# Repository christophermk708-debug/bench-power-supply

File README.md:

# bench-power-supply
# Adjustable Bench Power Supply

A from-scratch benchtop power supply: adjustable 1.4–11.9 V buck-regulated main output with live voltage/current display, plus fixed 5 V and 3.3 V rails. Designed in KiCad, fabricated by JLCPCB, hand-assembled, and brought up with a staged test procedure. 

## Specifications (measured)

| Parameter | Value |
|---|---|
| Input | 12 V DC barrel jack (center-positive, regulated) |
| Adjustable output | **1.4 – 11.9 V** (25-turn trimmer), ~2 A class |
| Fixed rails | 5.0 V (L7805) and 3.3 V (AMS1117) on headers |
| Metering | Panel voltmeter/ammeter on the adjustable output |
| Protection | Reverse-polarity Schottky (1N5822), 3 A resettable PTC fuse, per-rail decoupling |

## Design

- **LM2596-ADJ buck converter** for the main rail-switching regulation chosen over linear for efficiency at multi-amp loads. Output set by a feedback divider: `Vout = 1.23 × (1 + R_upper/R_lower)`, with a 25-turn trimmer as the adjustable element.
- **Fixed rails cascade from the buck's input**: the 7805 drops 12 V→5 V and the AMS1117 is fed *from the 5 V rail* rather than raw input to minimize dissipation.
- **Layout follows switching-supply practice**: the LM2596/inductor/catch-diode/capacitor loop is clustered tightly to minimize the switching current loop.

## Rev A findings — what the first board taught me

Every one of these was found by measurement during bring-up.

1. **D1 (reverse-polarity diode) was oriented backwards *in the schematic*.** The silkscreen reproduced the error, so the assembled board matched the design and this blocked all input power. Found by voltage tracing: ~12 V on the jack side of D1, ~1 V after it. Invisible to DRC and 3D review because the error was electrical, not mechanical. Fixed by desoldering and flipping the part.
2. **Maximum output was limited to 8.6 V by the feedback divider**, not by input headroom. Derived from the regulation equation: with R_lower = 1 kΩ, max Vout = 1.23 × (1 + 6k/1k) ≈ 8.6 V. Reworked R1 from 1 kΩ → 470 Ω on-board, raising the measured maximum to 11.9 V.
3. **J1 barrel jack footprint was placed rotated 180°** — the connector opening faced into the board. Resolved by flipping the 

## Bring-up lessons 

- A "12 V" wall adapter measured **25 V with no load**  it was an unregulated transformer type that only reaches nameplate under rated current. Replaced with a regulated switching adapter; my acceptance test is now a bare-plug measurement before any adapter touches a board.
- Mid-debug, **every reading came in almost exactly 2× high**  input, both fixed rails, even a USB 5 V reference. The multimeter's factory-included battery was dying, skewing its reference. Verified against known references (fresh AA cell, USB 5 V, the panel meter) before condemning any hardware. Lesson: when every measurement is wrong by the same factor, suspect the instrument first.

## Bring-up procedure

Staged and gated: visual inspection → continuity short-hunt on every rail  → adapter verification  → first power with no load, rail-by-rail measurement → potentiometer sweep across the full range → panel-meter cross-calibration against the DMM → first real load. No stage proceeds until the previous one passes.

## Rev B changes

- D1 orientation corrected in schematic
- J1 footprint rotated 180°
- R1 = 470 Ω for full output range

## Files

- `kicad/` — schematic and PCB source
- `gerbers/` — fabrication files as sent to JLCPCB
- `images/` — renders and build photos

## First real job

This supply's first load was my PID temperature controller — the panel ammeter visibly tracks the controller's PWM duty as it regulates.

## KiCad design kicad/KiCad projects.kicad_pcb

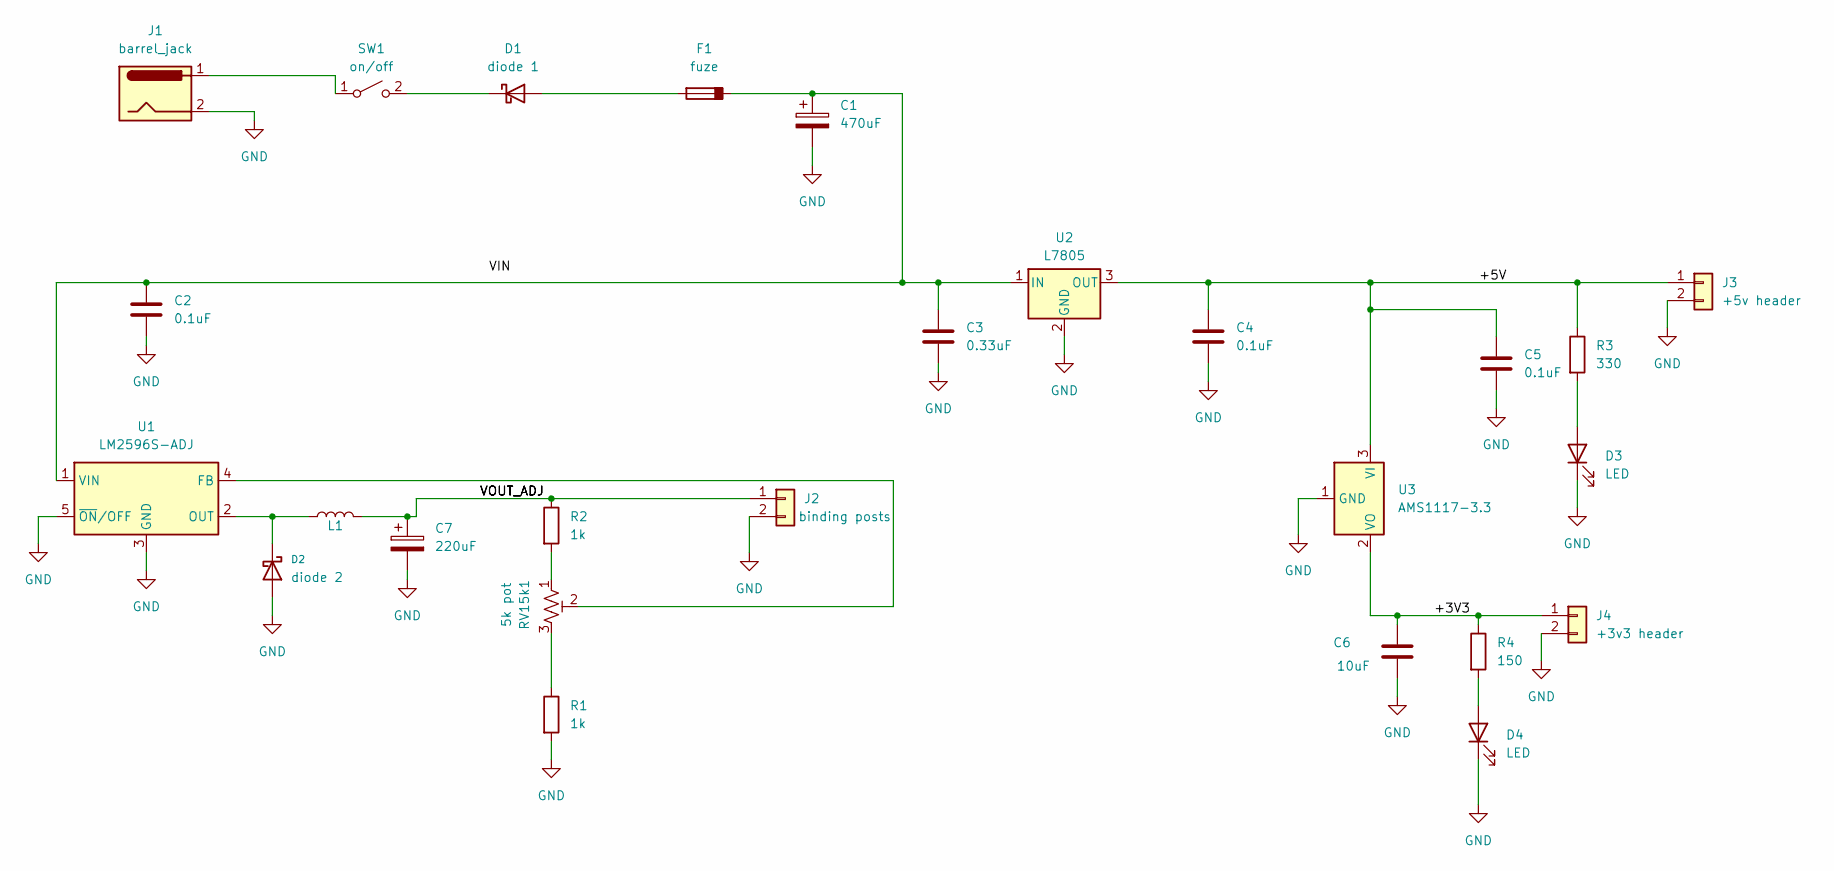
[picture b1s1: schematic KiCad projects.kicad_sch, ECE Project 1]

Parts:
C1: 470uF; CP_Radial_D10.0mm_P5.00mm
C2, C4, C5: 0.1uF; C_Disc_D5.0mm_W2.5mm_P2.50mm
C3: 0.33uF; C_Disc_D5.0mm_W2.5mm_P2.50mm
C6: 10uF; C_Disc_D5.0mm_W2.5mm_P2.50mm
C7: 220uF; CP_Radial_D10.0mm_P5.00mm
D1: diode 1; P2_DO-201
D2: diode 2; P2_DO-201
D3, D4: LED; LED_D3.0mm
F1: fuze; C_Disc_D11.0mm_W5.0mm_P5.00mm
J1: barrel_jack; BarrelJack_CUI_PJ-102AH_Horizontal
J2: binding posts; PinHeader_1x02_P2.54mm_Horizontal
J3: +5v header; PinHeader_1x02_P2.54mm_Horizontal
J4: +3v3 header; PinHeader_1x02_P2.54mm_Horizontal
L1: L; IND_BOURNS_RLB0914
R1, R2: 1k; R_Axial_DIN0207_L6.3mm_D2.5mm_P7.62mm_Horizontal
R3: 330; R_Axial_DIN0207_L6.3mm_D2.5mm_P7.62mm_Horizontal
R4: 150; R_Axial_DIN0207_L6.3mm_D2.5mm_P7.62mm_Horizontal
RV15k1: 5k pot; Potentiometer_Bourns_3296W_Vertical
SW1: on/off; PinHeader_1x02_P2.54mm_Horizontal
U1: LM2596S-ADJ; T05D
U2: L7805; TO-220_STM
U3: AMS1117-3.3; SOT-223-3_TabPin2

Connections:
/+3V3: C6.1, J4.1, R4.1, U3.2 (VO)
/+5V: C4.1, C5.1, J3.1, R3.1, U2.3 (OUT), U3.3 (VI)
GND: C1.2, C2.2, C3.2, C4.2, C5.2, C6.2, C7.2, D2.2 (A), D3.1 (K), D4.1 (K), J1.2, J2.2, J3.2, J4.2, R1.2, U1.3 (GND), U1.5 (~ON/OFF), U2.2 (GND), U3.1 (GND)
unnamed: D1.2 (A), F1.2
unnamed: D1.1 (K), SW1.2 (B)
unnamed: D2.1 (K), L1.1, U1.2 (OUT)
unnamed: D3.2 (A), R3.2
unnamed: D4.2 (A), R4.2
unnamed: C7.1, J2.1, L1.2, R2.1
unnamed: R1.1, RV15k1.3
unnamed: R2.2, RV15k1.1
unnamed: J1.1, SW1.1 (A)
unnamed: RV15k1.2, U1.4 (FB)
unnamed: C1.1, C2.1, C3.1, F1.1, U1.1 (VIN), U2.1 (IN)

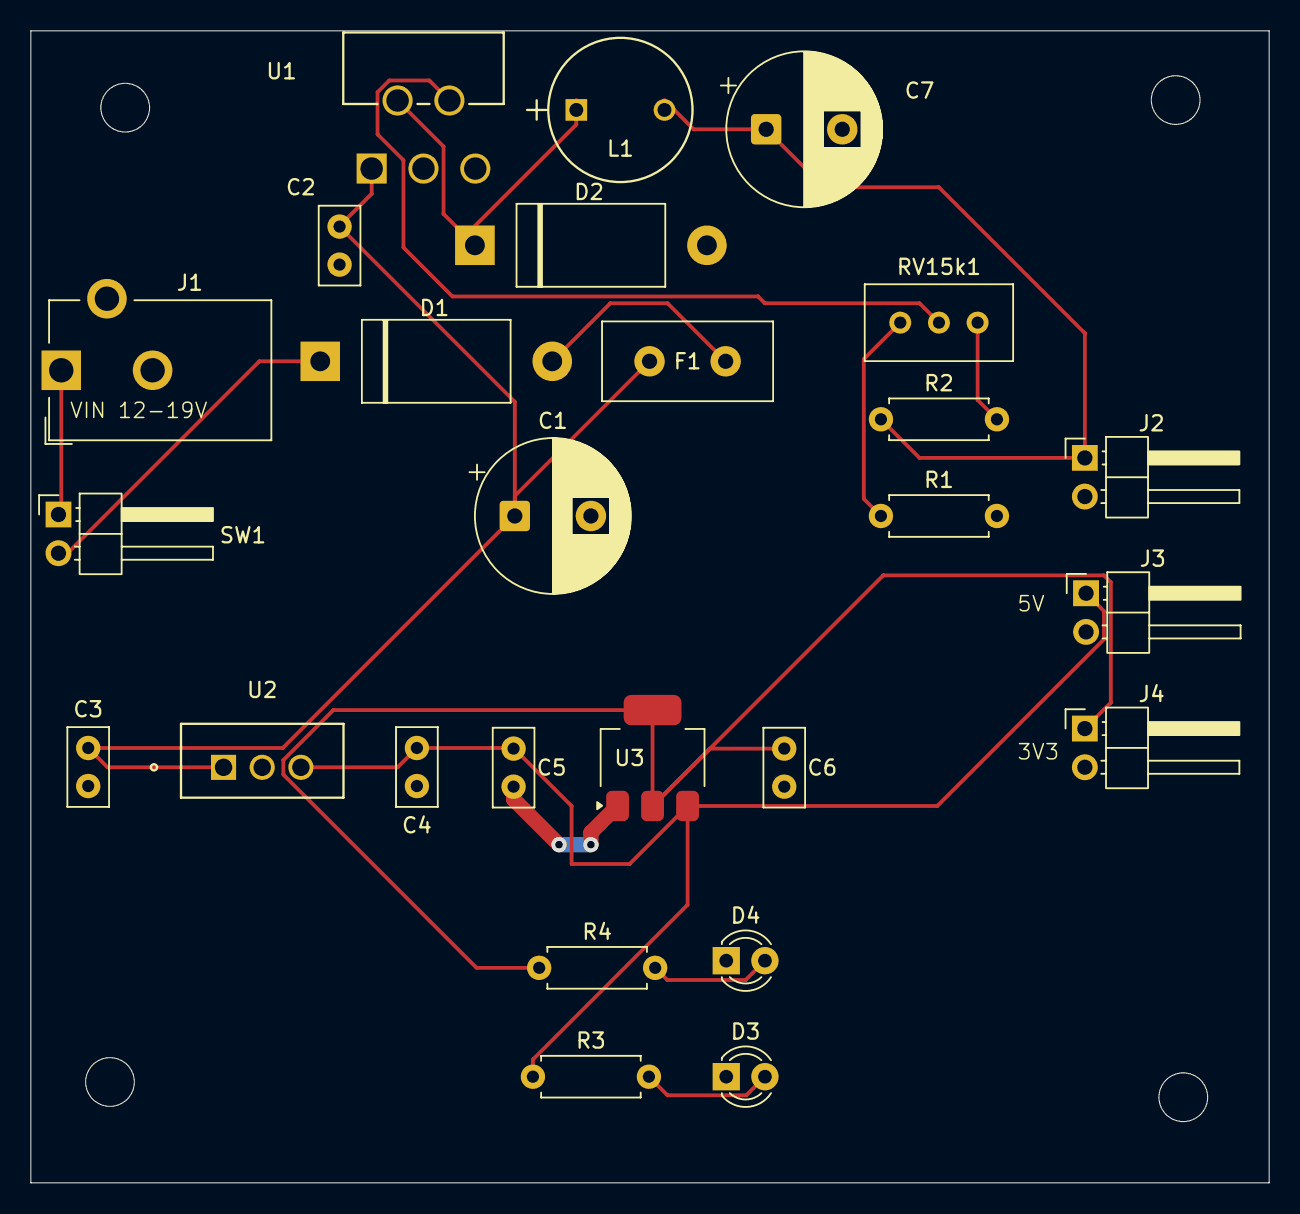
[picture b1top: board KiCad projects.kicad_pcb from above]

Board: 2 copper layers, 81.3 x 75.7 mm, 26 parts (0 on the bottom side), 14 nets.
